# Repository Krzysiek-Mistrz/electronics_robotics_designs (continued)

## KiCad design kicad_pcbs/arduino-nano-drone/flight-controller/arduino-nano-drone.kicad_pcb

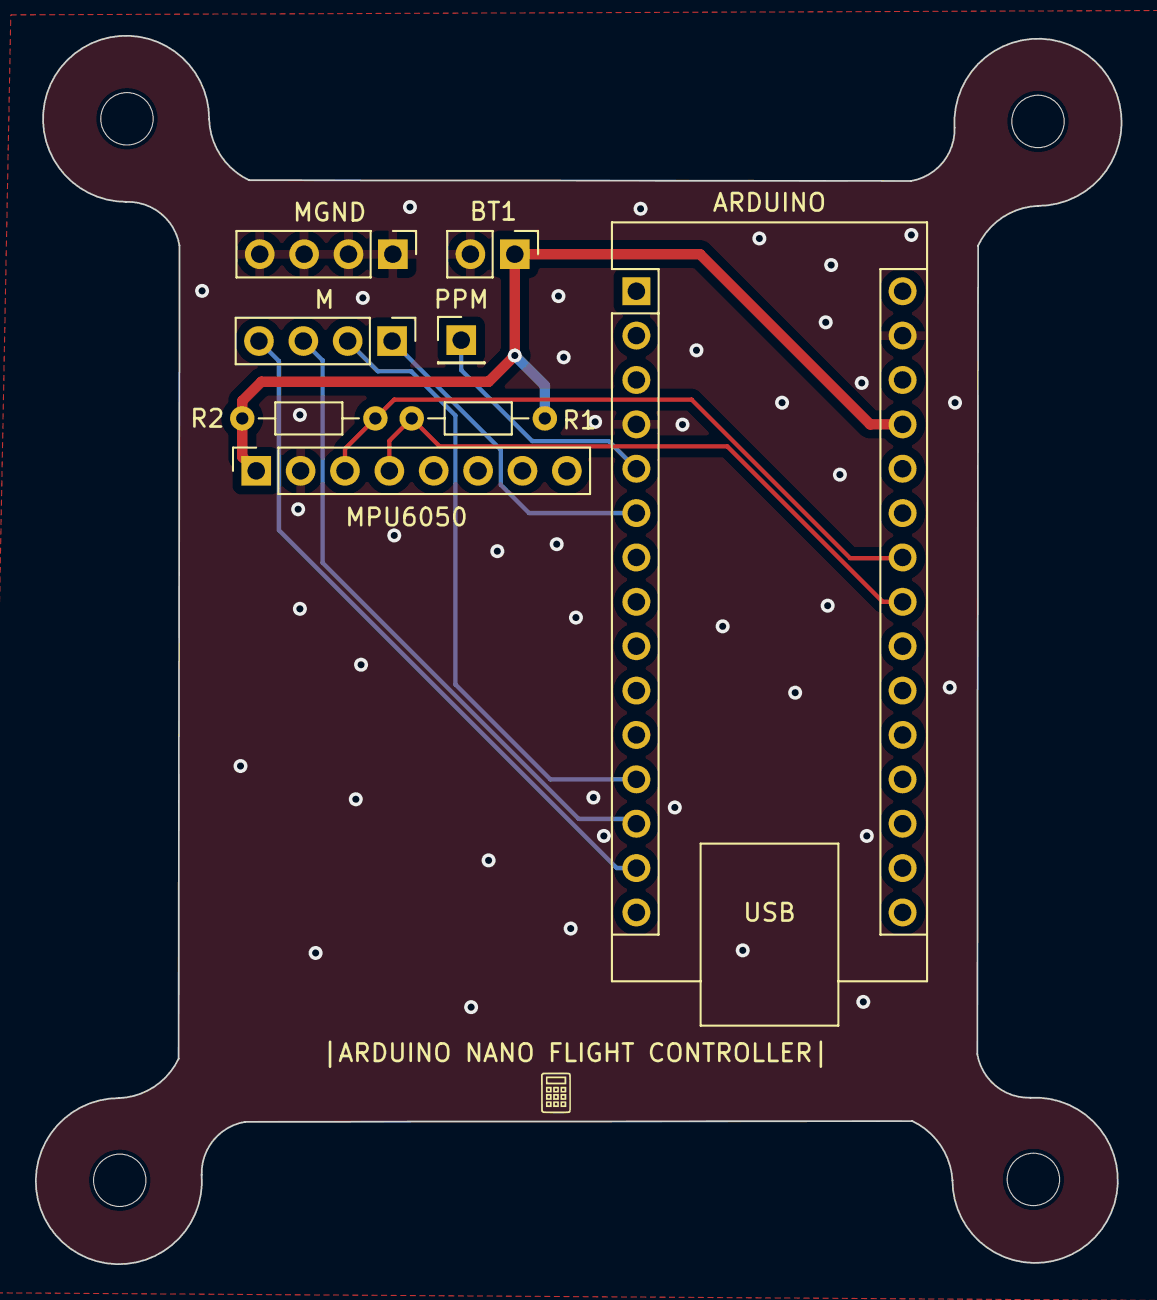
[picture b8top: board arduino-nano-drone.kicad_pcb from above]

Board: 2 copper layers, 62.2 x 70.3 mm, 8 parts (0 on the bottom side), 9 nets.

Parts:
ARDUINO: Arduino_Nano_v2.x; Arduino_Nano
BT1: Battery; PinHeader_1x02_P2.54mm_Vertical
M: Conn_01x04_Pin; PinHeader_1x04_P2.54mm_Vertical
MGND: motors pins; PinHeader_1x04_P2.54mm_Vertical
MPU6050: mpu6050 socket pins; PinSocket_1x08_P2.54mm_Vertical
PPM: Conn_01x01_Pin; PinHeader_1x01_P2.54mm_Vertical
R1, R2: 4.7k; R_Axial_DIN0204_L3.6mm_D1.6mm_P7.62mm_Horizontal

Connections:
/SCL: ARDUINO.24 (A5), MPU6050.3, R2.2
/SDA: ARDUINO.23 (A4), MPU6050.4, R1.2
GND: ARDUINO.4 (GND), ARDUINO.29 (GND), BT1.2 (-), MGND.1, MGND.2, MGND.3, MGND.4, MPU6050.2
unnamed: ARDUINO.5 (D2), PPM.1
unnamed: ARDUINO.6 (D3), M.1
unnamed: ARDUINO.12 (D9), M.2
unnamed: ARDUINO.13 (D10), M.3
unnamed: ARDUINO.14 (D11), M.4
VCC: ARDUINO.27 (+5V), BT1.1 (+), MPU6050.1, R1.1, R2.1

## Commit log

2023-08-20 ne555 servo controller
2023-08-29 l293d motor controller
2023-08-29 commit 0 / readme added
2023-09-11 project 1 / ne555 servo controller / new circuit added
2023-09-11 project 3 / l293 motor driver / changed tracks dimensions
2023-09-11 project 0 / readme / commit mess added
2023-09-11 project 6 / bc546b astable multivibrator / added new circuit
2023-09-11 removing additional files
2023-09-11 project 3 / l293d motor driver / l293 motor driver added f.t.f.t
2023-09-11 project 5 / models / added some 3d models for lampolov and speedy
2023-09-11 project 3 / l293d motor driver / l293d project added
2023-09-11 project 4 / additional files / kicad library added
2023-09-11 project 3 / l293d motor driver / design improved
2023-09-11 project 4 / additional files / pcb logo added
2023-09-11 project 0 / readme / changed commit message and added clarification ab project
2023-09-11 project 3 / l293 motor driver / tracks reworked
2023-09-11 project 3 / l293d motor driver / layout improvement
2023-09-11 removing addit_files
2023-09-12 project 3 / l293d motor driver / 74hc04 changed to cd4069
2023-09-13 project 7 / cd4069 siren / added schematics
2023-09-13 project 3 / l293d motor driver / pcb layout improved
2023-09-13 project 3 / l293d motor controller / improved tracs
2023-09-14 project 3 / l293d motor driver / VCC track changed
2023-09-14 project 7 / cd4069 siren / added footprints and designed layout for pcb components
2023-09-15 project 3 / l293d motor driver / fab added
2023-09-16 project 7 / cd4069 siren / changed edge cuts, improved tracks, added logo
2023-09-16 project 4 / additional files / added 30mm and 4mm pcblogo
2023-09-19 project 7 / cd4069 siren / addi backup files
2023-09-19 project 8 / arduino nano drone / added project
2023-09-19 project 4 / additional files / arduino drone model
2023-09-21 project 8 / arduino nano drone / added transmitter project
2023-09-30 project 7 / cd4069 siren / fab added
2023-09-30 project 8 / arduino nano drone / flight controller improved
2023-09-30 project 8 / arduino nano drone / added radio transmitter and improved schematics
2023-09-30 project 3 / l293d motor driver / project modified
2023-09-30 project 5 / models / drone model improved
2023-09-30 project 6 / bc546b astable multivibrator / added fab, improved circuit
2023-10-01 project 8 / arduino nano drone / added rt, rr, fl pcb, improved layout
2023-10-01 project 3 / l293d motor driver / minor changes
2023-10-01 project 4 / additional files / pcb logo dim:40x40 added
2023-10-02 Reviewed schematics and boards
2023-10-04 project 8 / arduino nano drone / improved schematics and pcb layout
2023-10-09 project 8 / arduino nano drone / improved schematics, pcb after review
2023-10-09 project 6 / bc546b astable multivibrator / improved schematics, pcb after review
2023-10-09 project 7 / cd4069 siren / improved schematics and pcb after review
2023-10-12 project 9 / arduino nano line follower / added pcb
2023-10-12 project 9 / arduino nano line follower / added_schematic
2023-10-15 project 9 / arduino nano line follower / improved connections
2023-10-16 project * / fabrication added for siren, multivibrator, drone, line-follower
2023-11-27 project * / codes for DIY projects
2023-12-02 few models added and some 3d models improved
2023-12-02 5030 propeller models added for drone
2024-08-22 new projects added (stm32 drone, linefollower esp, ...
2024-08-22 changed readme
2025-05-12 deleted old repo structure & files
2025-05-12 added working code for drone fc built on stm32f103
2025-05-12 added linefollwer codes for both arduino & esp32 last edition for both is the final working one
2025-05-12 added electronics designs built in altium
2025-05-12 added basic docs for robitic arm manipulator there are also some docs with code within
2025-05-12 added additional projects i built in the meantime
2025-05-12 added models and reorganized prev structure of old prj
2025-05-12 added docs to prj
2025-05-12 added code plan for vacuum prj
2025-05-12 updated README & updated some file in linefollower prj
2025-05-12 added .gitmodule and LICENSE to robotics codes
2025-05-12 reupdated AOVV
2025-05-12 deleted unnecesarry AOVV code
